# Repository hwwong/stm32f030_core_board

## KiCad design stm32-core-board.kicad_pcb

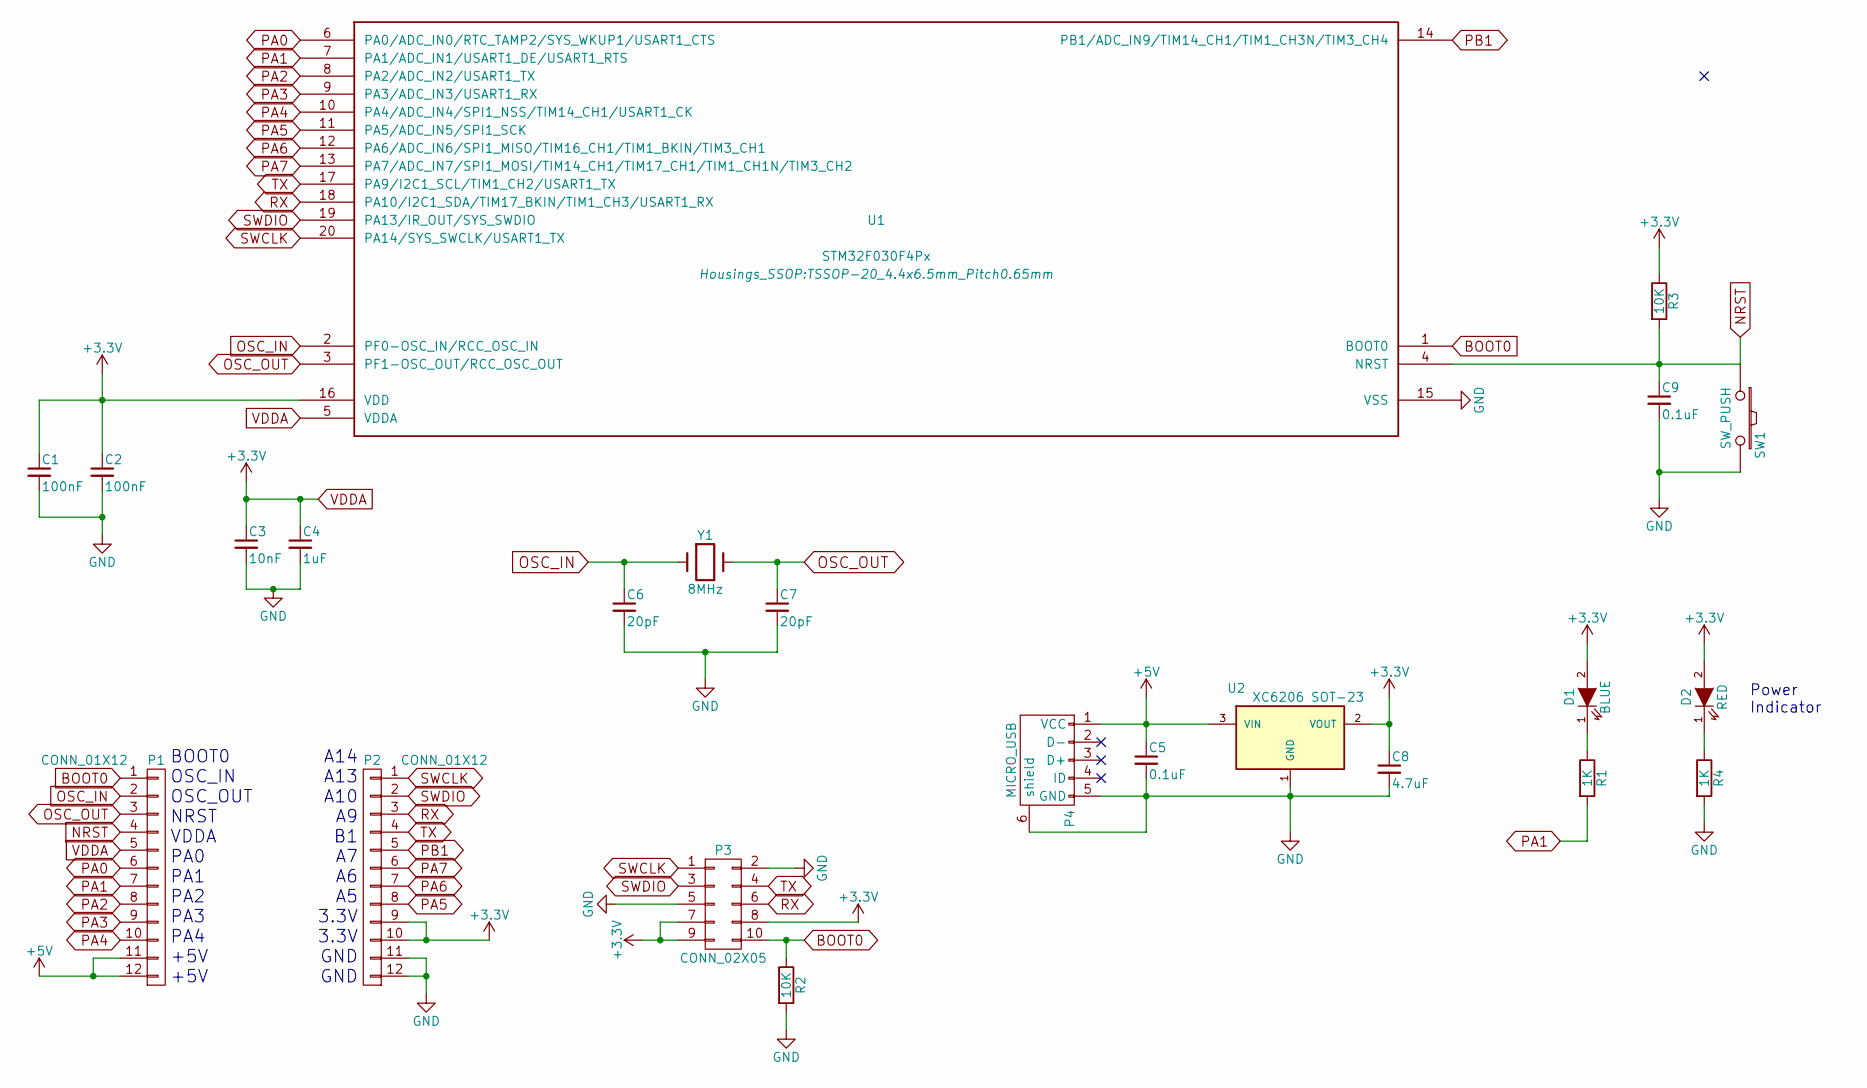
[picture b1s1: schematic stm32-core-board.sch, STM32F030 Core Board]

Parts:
C1, C2: 100nF; C_0603_HandSoldering
C3: 10nF; C_0603_HandSoldering
C4: 1uF; C_0603_HandSoldering
C5, C9: 0.1uF; C_0603_HandSoldering
C6, C7: 20pF; C_0603_HandSoldering
C8: 4.7uF; C_0603_HandSoldering
D1: BLUE; LED-0603
D2: RED; LED-0603
P1, P2: CONN_01X12; Pin_Header_Straight_1x12
P3: CONN_02X05; Pin_Header_Straight_2x05
P4: MICRO_USB; USB_Micro-B_MK5P
R1, R4: 1K; R_0603_HandSoldering
R2, R3: 10K; R_0603_HandSoldering
SW1: SW_PUSH; SW_SPST_EVQPE1
U1: STM32F030F4Px; TSSOP-20_4.4x6.5mm_Pitch0.65mm
U2: XC6206 SOT-23; SOT-23
Y1: 8MHz; Crystal_HC49-SD_SMD

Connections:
+5V: C5.1, P1.11, P1.12, P4.1 (VCC), U2.3 (VIN)
BOOT0: P1.1, P3.10, R2.1, U1.1 (BOOT0)
GND: C1.2, C2.2, C3.2, C4.2, C5.2, C6.2, C7.2, C8.2, C9.2, P2.11, P2.12, P3.2, P3.5, P4.5 (GND), P4.6 (shield), R2.2, R4.2, SW1.2, U1.15 (VSS), U2.1 (GND)
NRST: C9.1, P1.4, R3.2, SW1.1, U1.4 (NRST)
unnamed: D1.1 (K), R1.1
unnamed: D2.1 (K), R4.1
OSC_IN: C6.1, P1.2, U1.2 (PF0-OSC_IN/RCC_OSC_IN), Y1.1
OSC_OUT: C7.1, P1.3, U1.3 (PF1-OSC_OUT/RCC_OSC_OUT), Y1.2
PA0: P1.6, U1.6 (PA0/ADC_IN0/RTC_TAMP2/SYS_WKUP1/USART1_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)
PA1: P1.7, R1.2, U1.7 (PA1/ADC_IN1/USART1_DE/USART1_RTS)
PA2: P1.8, U1.8 (PA2/ADC_IN2/USART1_TX)
PA3: P1.9, U1.9 (PA3/ADC_IN3/USART1_RX)
PA4: P1.10, U1.10 (PA4/ADC_IN4/SPI1_NSS/TIM14_CH1/USART1_CK)
PA5: P2.8, U1.11 (PA5/ADC_IN5/SPI1_SCK)
PA6: P2.7, U1.12 (PA6/ADC_IN6/SPI1_MISO/TIM16_CH1/TIM1_BK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)
PA7: P2.6, U1.13 (PA7/ADC_IN7/SPI1_MOSI/TIM14_CH1/TIM17_C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)
PB1: P2.5, U1.14 (PB1/ADC_IN9/TIM14_CH1/TIM1_CH3N/TIM3_CH4)
RX: P2.3, P3.6, U1.18 (PA10/I2C1_SDA/TIM17_BKIN/TIM1_CH3/USART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)
SWCLK: P2.1, P3.1, U1.20 (PA14/SYS_SWCLK/USART1_TX)
SWDIO: P2.2, P3.3, U1.19 (PA13/IR_OUT/SYS_SWDIO)
TX: P2.4, P3.4, U1.17 (PA9/I2C1_SCL/TIM1_CH2/USART1_TX)
VDDA: C1.1, C2.1, C3.1, C4.1, C8.1, D1.2 (A), D2.2 (A), P1.5, P2.9, P2.10, P3.7, P3.8, P3.9, R3.1, U1.5 (VDDA), U1.16 (VDD), U2.2 (VOUT)

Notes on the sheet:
Power Indicator
BOOT0 OSC_IN OSC_OUT NRST VDDA PA0 PA1 PA2 PA3 PA4 +5V +5V
A14 A13 A10 A9 B1 A7 A6 A5 3.3V 3.3V GND GND

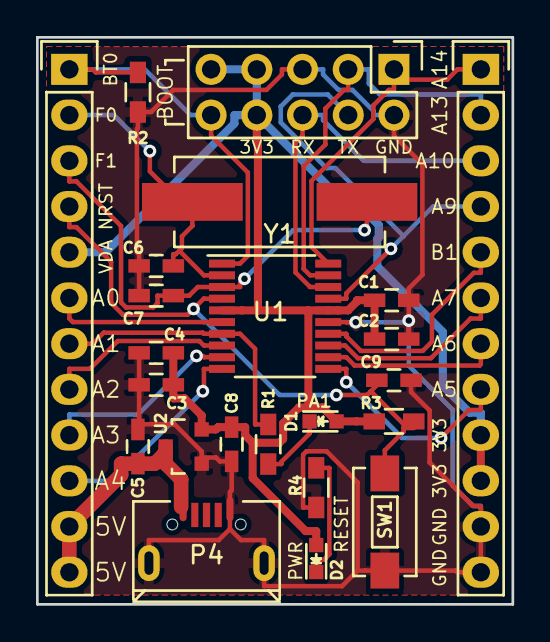
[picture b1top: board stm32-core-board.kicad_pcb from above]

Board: 2 copper layers, 26.4 x 31.5 mm, 23 parts (0 on the bottom side), 22 nets.

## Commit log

2016-06-08 Upload all file
